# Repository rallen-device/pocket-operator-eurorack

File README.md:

# Pocket Operator Eurorack

Hardware for converting a teenage engineering pocket operator to be eurorack compatible.

Slots onto the back of the pocket operator. Requires soldering to the audio jacks + battery connectors.
Splits stereo input + output in two mono channels for each allowing separation of clock + audio.

Fits into a standard eurorack 3U case with width of 14HP.

# Relevant

3D step model of a pocket operator was created for this project. It can be found on grabcad: https://grabcad.com/library/teenage-engineering-pocket-operator-1

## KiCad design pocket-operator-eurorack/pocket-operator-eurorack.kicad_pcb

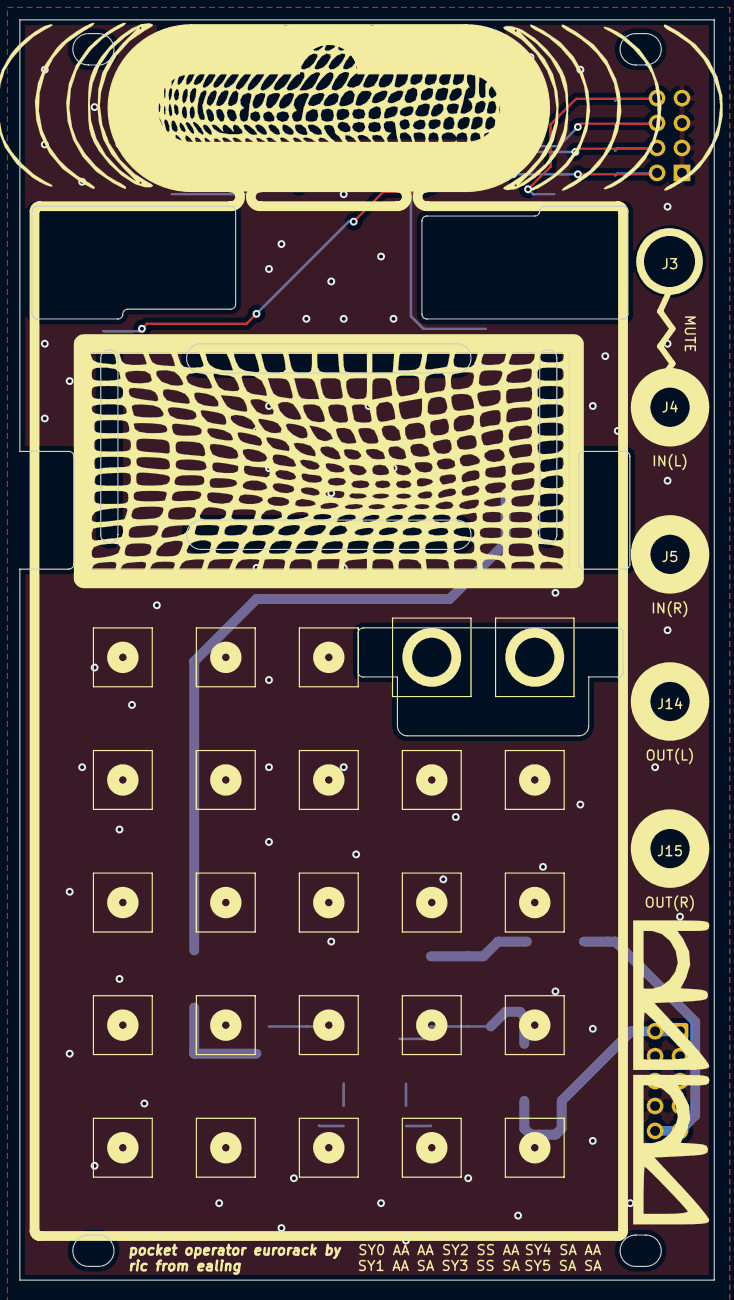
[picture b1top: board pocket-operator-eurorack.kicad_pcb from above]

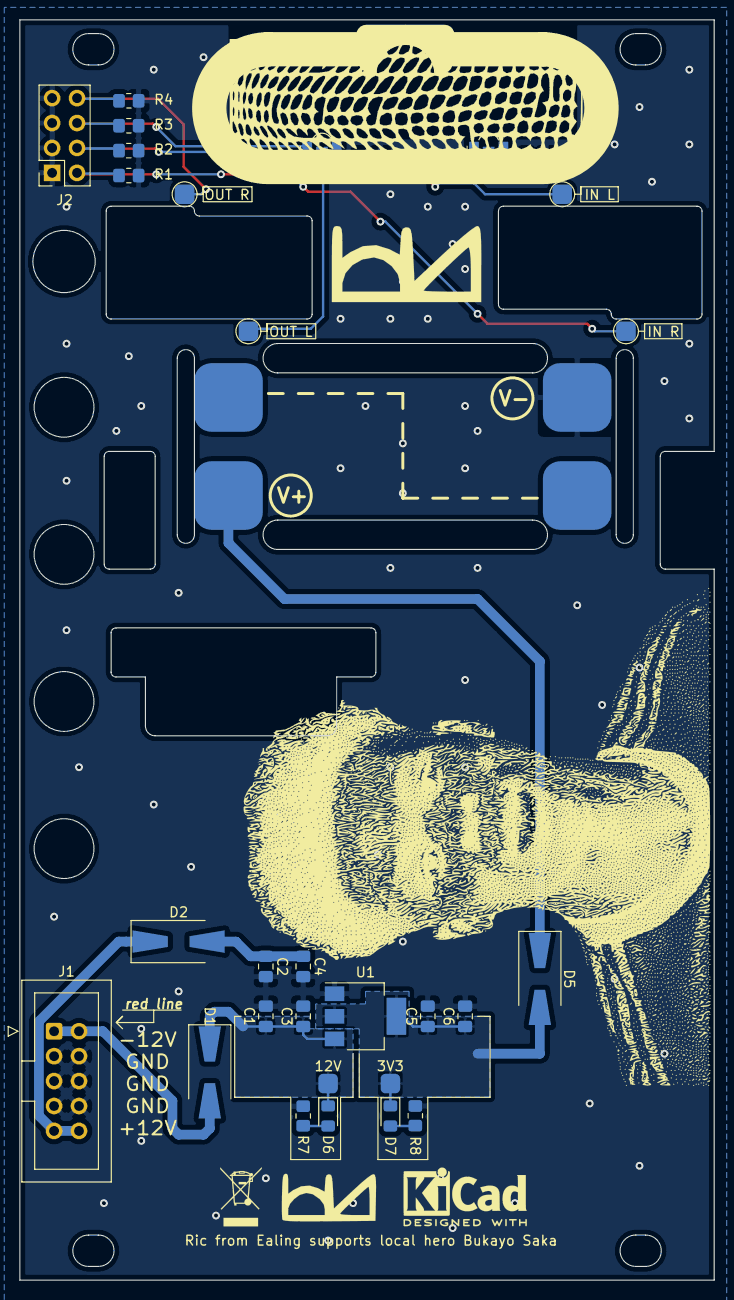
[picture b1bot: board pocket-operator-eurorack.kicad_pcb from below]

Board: 2 copper layers, 70.8 x 128.5 mm, 39 parts (34 on the bottom side), 15 nets.

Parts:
C1, C2, C3, C4, C5, C6: C; C_0805_2012Metric_Pad1.18x1.45mm_HandSolder
D1, D2, D5: D; D_SMA-SMB_Universal_Handsoldering
D3, D4: LED; LED_Kingbright_APFA3010_3x1.5mm_Horizontal
D6, D7: LED; LED_0805_2012Metric_Pad1.15x1.40mm_HandSolder
J1: Conn_02x05_Odd_Even; IDC-Header_2x05_P2.54mm_Vertical
J2: Conn_02x04_Odd_Even; PinSocket_2x04_P2.54mm_Vertical
J3: SW_6mm_panel
J4, J5, J14, J15: Thonkiconn_PJ398SM_panel
J6, J7, J8, J9, J16, J17: Conn_01x01; 2mm_solder_pad
J10, J11, J12, J13: Conn_01x01; 7mm_solder_pad
R1, R2, R3, R4, R5, R6, R7, R8: R; R_0805_2012Metric_Pad1.20x1.40mm_HandSolder
U1: NCP1117-3.3_SOT223; SOT-223-3_TabPin2

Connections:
+3V3: D5.1, J10.1
+12V: C1.1, C3.1, D1.1, D6.1, J16.1, U1.3
-12V: C2.1, C4.1, D2.2
/IN_L: D3.1, J2.2, J8.1, R1.1
/IN_R: J2.4, J6.1, R2.1
/OUT_L: D4.1, J2.6, J9.1, R3.1
/OUT_R: J2.8, J7.1, R4.1
GND: C1.2, C2.2, C3.2, C4.2, C5.2, C6.2, J1.3, J1.4, J1.5, J1.6, J1.7, J1.8, J2.1, J2.3, J2.5, J2.7, J11.1, R1.2, R2.2, R3.2, R4.2, R5.2, R6.2, R7.2, R8.2, U1.1
unnamed: C5.1, C6.1, D5.2, D7.1, J17.1, U1.2
unnamed: D1.2, J1.1, J1.2
unnamed: D2.1, J1.9, J1.10
unnamed: D3.2, R5.1
unnamed: D4.2, R6.1
unnamed: D6.2, R7.1
unnamed: D7.2, R8.1

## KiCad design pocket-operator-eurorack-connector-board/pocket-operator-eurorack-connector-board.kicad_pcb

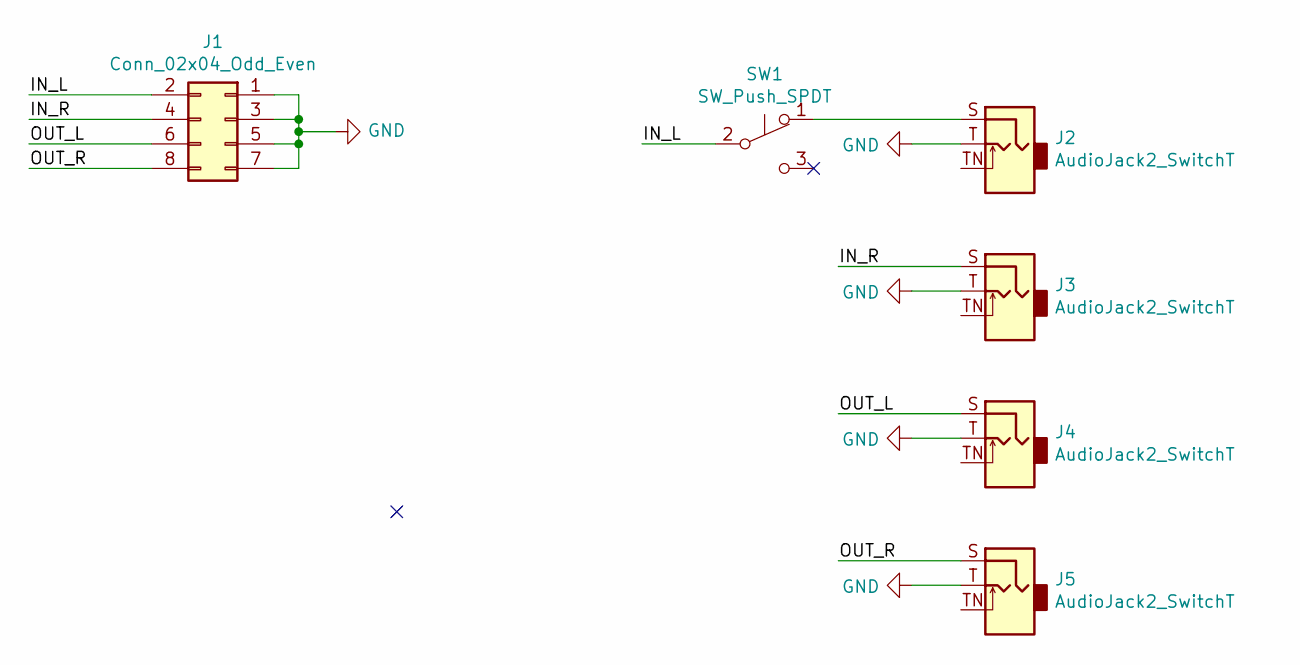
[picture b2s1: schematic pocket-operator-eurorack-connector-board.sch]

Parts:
J1: Conn_02x04_Odd_Even; PinHeader_2x04_P2.54mm_Vertical
J2, J3, J4, J5: AudioJack2_SwitchT; Jack_3.5mm_QingPu_WQP-PJ398SM_Vertical
SW1: SW_Push_SPDT; SW_6mm_SPDT

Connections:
/IN_L: J1.2, SW1.2 (B)
/IN_R: J1.4, J3.S
/OUT_L: J1.6, J4.S
/OUT_R: J1.8, J5.S
GND: J1.1, J1.3, J1.5, J1.7, J2.T, J3.T, J4.T, J5.T
unnamed: J2.S, SW1.1 (A)

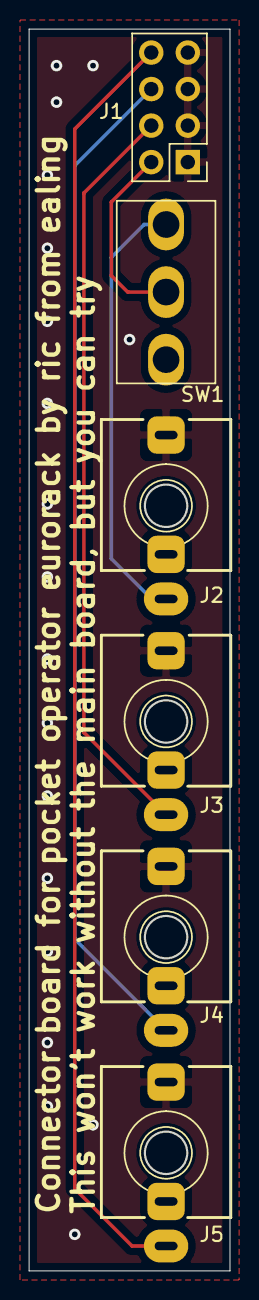
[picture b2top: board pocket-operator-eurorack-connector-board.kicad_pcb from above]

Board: 2 copper layers, 13.9 x 86.3 mm, 6 parts (0 on the bottom side), 6 nets.

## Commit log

2021-12-24 readme added
2021-12-26 update to kicad cut outs
2021-12-26 kicad silkscreen updated
2021-12-26 front silkscreen artwork finished
2021-12-27 components selected and placed on board, need to confirm that gnds are connector to each other and that in/out pads are placed correctly
2021-12-27 all tracks tracked, everything added, ready to be reviewed
2021-12-27 connector board added, main board changed to fit connectors correctly
2021-12-27 connector board placed and tracked
2021-12-27 connector board updated
2021-12-27 connector board finalised, ready for review
2021-12-27 freecad files added to gitignore
2021-12-30 finished and gerbers sent off for production
2021-12-30 readme updated
